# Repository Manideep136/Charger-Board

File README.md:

# Charger-Board

TP4056 Lithium-Ion Battery Charger Board

📌 Project Overview

This project presents the design and implementation of a Lithium-Ion Battery Charger Board using the TP4056 IC. The TP4056 is a complete constant-current/constant-voltage linear charger designed for charging single-cell lithium-ion and lithium-polymer batteries.

The charger board accepts 5V input through a USB Type-C connector and safely charges a 3.7V Li-ion battery with charging status indication using LEDs.

The schematic and PCB are designed using KiCad.

🔧 Components Used
Component	Value
TP4056-42-ESOP8	Battery Charging IC
USB Type-C Connector	Power Input
Battery Connector	JST-PH 2-Pin
R1	1.2 kΩ
R2	1 kΩ
R3	1 kΩ
C1	10 µF
C2	10 µF
D1	Charging LED
D2	Fully Charged LED
⚡ Features
USB Type-C input
Supports single-cell 3.7V Li-ion/Li-Po batteries
Constant Current / Constant Voltage charging
Automatic charge termination
Charging status indication
Thermal regulation
Battery protection compatibility
Compact PCB design
🔌 Circuit Description

The TP4056 charger operates using the CC/CV charging method.

Stage 1: Constant Current Charging

The battery is charged with a fixed current determined by the resistor connected to the PROG pin.

Stage 2: Constant Voltage Charging

When the battery voltage reaches 4.2V, the TP4056 maintains a constant voltage and gradually reduces the charging current.

Charge Completion

Charging stops automatically when the charging current drops to approximately 10% of the programmed value.

Charging current:

Icharge ≈ 1000 mA
💡 LED Indication
LED Status	Meaning
CHRG LED ON	Charging
STDBY LED ON	Battery Fully Charged
🛠️ Software Used
KiCad
KiCad Schematic Editor
KiCad PCB Editor
ERC (Electrical Rules Check)
DRC (Design Rule Check)
📁 Project Structure
TP4056-Charger/
│
├── README.md
├── TP4056.kicad_sch
├── TP4056.kicad_pcb
├── Gerber/
├── Images/
│   ├── Schematic.png
│   └── PCB.png
└── Datasheet/
    └── TP4056.pdf
📦 Recommended Footprints
Component	Footprint
TP4056	SOIC-8-1EP_3.9x4.9mm
Resistors	R_0805
Capacitors	C_0805
LEDs	LED_0805
USB Type-C	Depends on connector
Battery Connector	JST_PH_2Pin
🚀 Applications
Power banks
Portable electronics
DIY battery packs
IoT devices
Wearable devices
Rechargeable gadgets
📷 Circuit Diagram

Add your KiCad schematic image:

📚 References
TP4056 Datasheet
KiCad Documentation
USB Type-C Specification
👨‍💻 Author

Manideep

Designed using KiCad for learning PCB design and battery charging circuits.

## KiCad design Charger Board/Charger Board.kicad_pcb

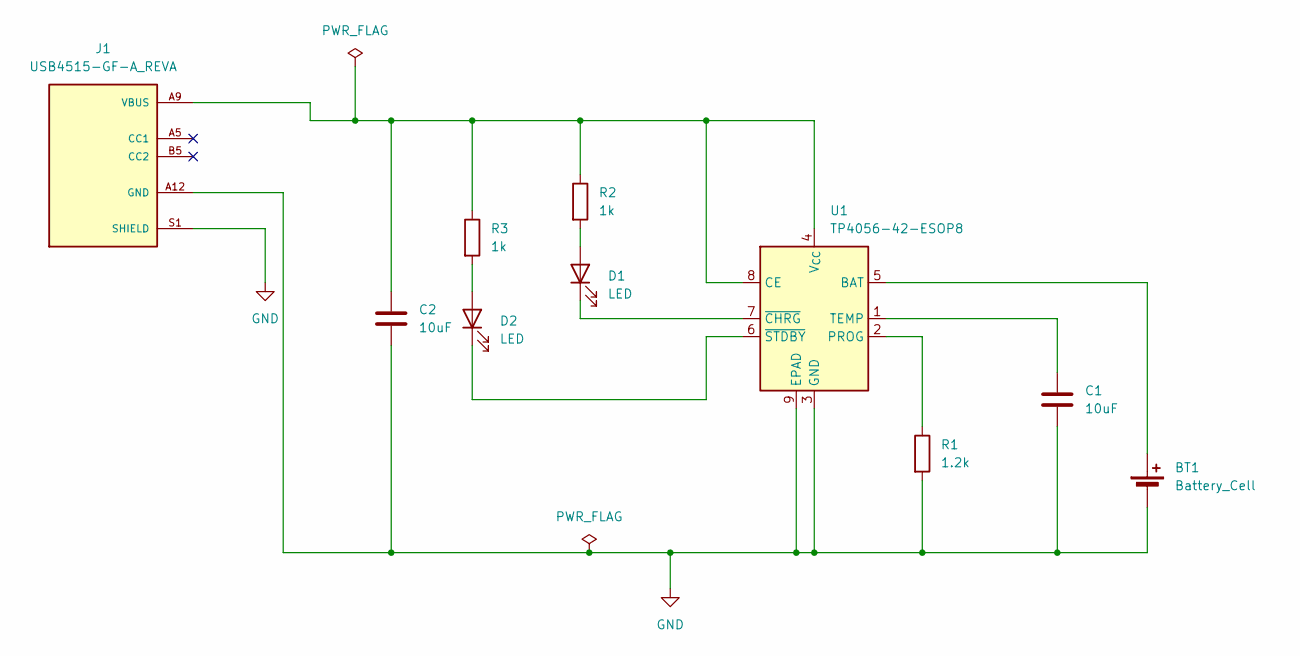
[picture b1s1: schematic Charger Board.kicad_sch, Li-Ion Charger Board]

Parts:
BT1: Battery_Cell; TerminalBlock_Phoenix_MKDS-1,5-2_1x02_P5.00mm_Horizontal
C1, C2: 10uF; C_0805_2012Metric
D1, D2: LED; D_0805_2012Metric
J1: USB4515-GF-A_REVA; GCT_USB4515-GF-A_REVA; PARTREV A
R1: 1.2k; R_0805_2012Metric
R2, R3: 1k; R_0805_2012Metric
U1: TP4056-42-ESOP8; SOIC-8-1EP_3.9x4.9mm_P1.27mm_EP2.41x3.3mm_ThermalVias

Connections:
GND: BT1.2 (-), C1.2, C2.2, J1.A12 (GND), J1.B12 (GND), J1.S1 (SHIELD), J1.S2 (SHIELD), J1.S3 (SHIELD), J1.S4 (SHIELD), R1.2, U1.3 (GND), U1.9 (EPAD)
unnamed: BT1.1 (+), U1.5 (BAT)
unnamed: D1.2 (A), R2.2
unnamed: D1.1 (K), U1.7 (~CHRG)
unnamed: D2.2 (A), R3.2
unnamed: D2.1 (K), U1.6 (~STDBY)
unnamed: R1.1, U1.2 (PROG)
unnamed: C1.1, U1.1 (TEMP)
VBUS: C2.1, J1.A9 (VBUS), J1.B9 (VBUS), R2.1, R3.1, U1.4 (V_{CC}), U1.8 (CE)

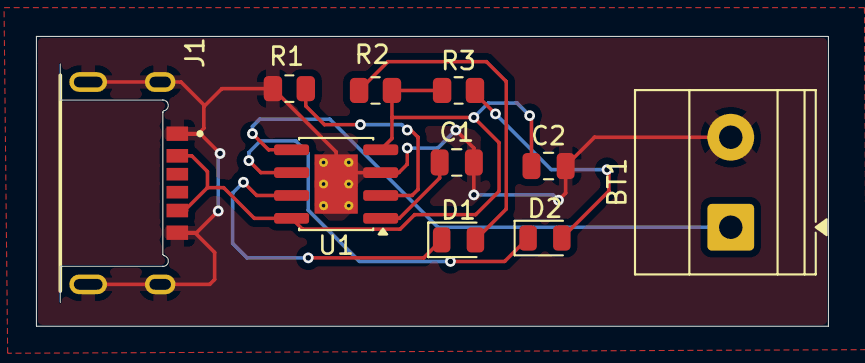
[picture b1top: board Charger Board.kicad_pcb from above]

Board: 2 copper layers, 44.0 x 16.1 mm, 10 parts (0 on the bottom side), 9 nets.
